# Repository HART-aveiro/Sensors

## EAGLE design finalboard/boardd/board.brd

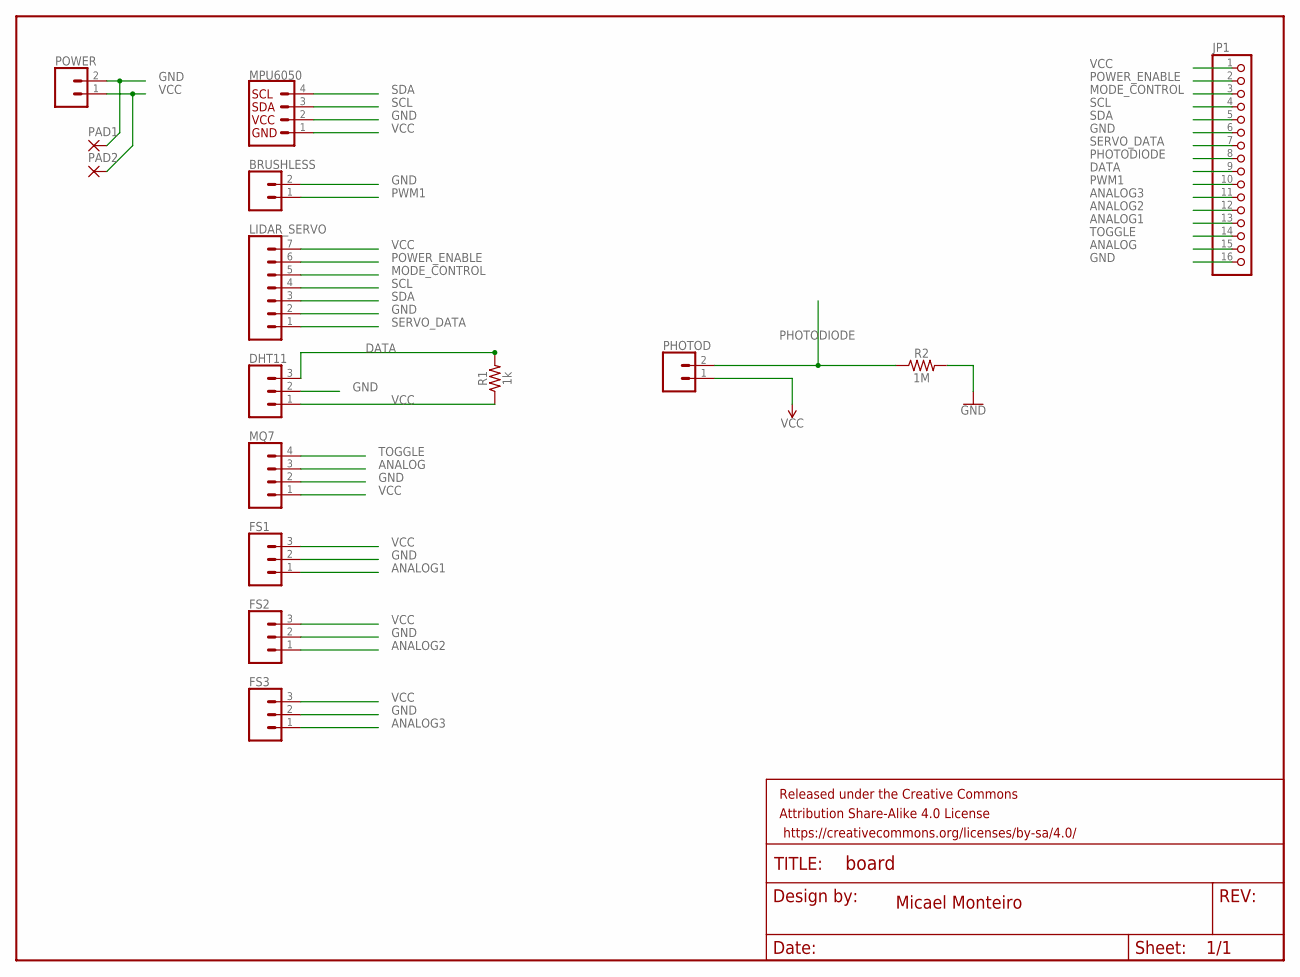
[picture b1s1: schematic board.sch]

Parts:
BRUSHLESS: CONN_02; 1X02
DHT11: CONN_03; 1X03
FRAME1: FRAME-LETTER; CREATIVE_COMMONS
FS1, FS2, FS3: CONN_03; 1X03
JP1: PINHD-1X16; 1X16
LIDAR_SERVO: CONN_07; 1X07
MPU6050: I2C_STANDARD; 1X04
MQ7: CONN_04; 1X04
PAD1, PAD2: 1,6/0,9
PHOTOD: CONN_02; 1X02
POWER: CONN_02; 1X02
R1: 1k; 0603
R2: 1M; 0603

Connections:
ANALOG: JP1.15, MQ7.3
ANALOG1: FS1.1, JP1.13
ANALOG2: FS2.1, JP1.12
ANALOG3: FS3.1, JP1.11
DATA: DHT11.3, JP1.9, R1.2
GND: BRUSHLESS.2, DHT11.2, FS1.2, FS2.2, FS3.2, JP1.6, JP1.16, LIDAR_SERVO.2, MPU6050.2, MQ7.2, PAD1.1, POWER.2, R2.2
MODE_CONTROL: JP1.3, LIDAR_SERVO.5
PHOTODIODE: JP1.8, PHOTOD.2, R2.1
POWER_ENABLE: JP1.2, LIDAR_SERVO.6
PWM1: BRUSHLESS.1, JP1.10
SCL: JP1.4, LIDAR_SERVO.4, MPU6050.3
SDA: JP1.5, LIDAR_SERVO.3, MPU6050.4
SERVO_DATA: JP1.7, LIDAR_SERVO.1
TOGGLE: JP1.14, MQ7.4
VCC: DHT11.1, FS1.3, FS2.3, FS3.3, JP1.1, LIDAR_SERVO.7, MPU6050.1, MQ7.1, PAD2.1, PHOTOD.1, POWER.1, R1.1

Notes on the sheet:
Micael Monteiro

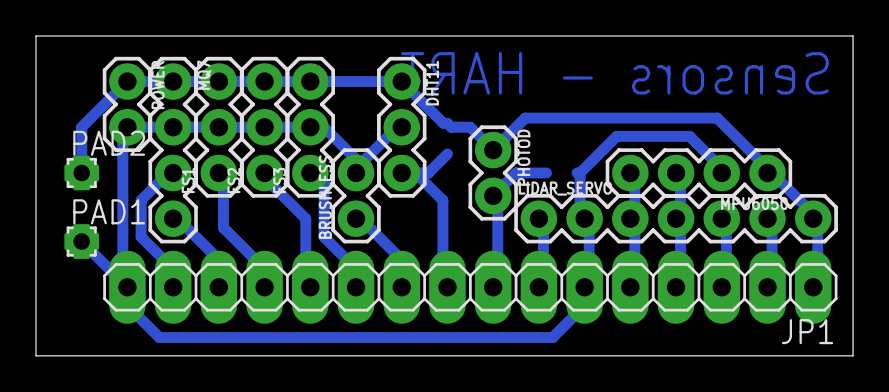
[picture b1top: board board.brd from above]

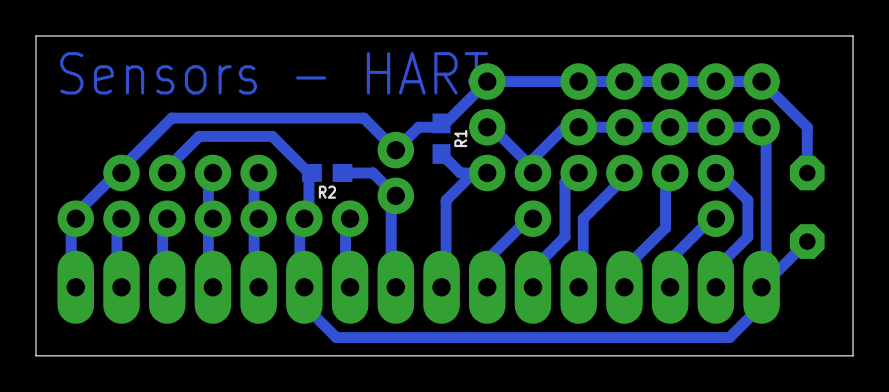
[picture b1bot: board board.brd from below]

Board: 2 copper layers, 45.4 x 17.8 mm, 16 parts (2 on the bottom side), 15 nets.

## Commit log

2017-04-26 Change main file name
2017-04-26 Added temp/hum lib
2017-04-28 Added dht11 code
2017-04-28 Added servo and brushless
2017-05-02 Total reshape of the code//Servo and brushless problem solved, Added simple feedback to brushless speed
2017-05-02 Working brush, servo, dht, mpu with debug from LEDs
2017-05-03 brushless velocity
2017-05-03 speedtrig functions added to hartimu
2017-05-03 Added MQ7 and corrected folders created by mistake
2017-05-03 PCB and flame sensors
2017-05-03 Added pcb files plus fire sensor API
2017-05-03 Added micael's work on flame sensor
2017-05-03 Temperature and humidity API
2017-05-03 Something happened and brushless atopped working :'(
2017-05-03 Semi works, problems in timing again :'(
2017-05-04 comunication code lines
2017-05-04 Working LIDAR @ 250HZ
2017-05-05 Latex documentation
2017-05-05 Removal of documentation
2017-05-05 Latex files
2017-05-05 removal
2017-05-05 removal latex files
2017-05-06 Corrected an error on line 420, bufMPU instead of bufLIDAR
2017-05-16 Not working
2017-05-17 Major changes to the code
2017-05-20 Comm working without lidar, new interrupt work method
2017-05-20 created gitIgnore for eagle's file
2017-05-20 All sensors working with comm without LIDAR
2017-05-20 Something is putting interrupt down
2017-05-20 conversa pedro
2017-05-20 Nao funciona e nao percebo porque, no comm, just MPU still fails, maybe an hardware problem, but don't know what it is :'(
2017-05-21 Deleted a empty line and added my email to git config
2017-05-23 Added lidar arduino code, need to test interrupt and ajust the time to 2778us Next step, introduce control from another arduino
2017-05-23 sensors.ino before correct freq
2017-05-23 Works all sensors without lidar, comm and pwm servos too
2017-05-23 Problems in MPU6050
2017-05-23 before pull
2017-05-24 Timer working at 360Hz
2017-05-24 Control for mega and lidar for uno without tests
2017-05-24 contact problems while testing
2017-05-26 working with voltage divider on pwm to servo
2017-05-26 working both arduino comm and sweep servo
2017-05-29 Sweep not working
2017-05-29 hartimu corrected
2017-05-29 Before upload after panda
2017-05-29 Sweep corrected but problems in timings
2017-05-29 Working LIDAR, sweep and brushless without comm
2017-05-31 all commented except lidar on loop
2017-05-31 Control is working, need a tweak
2017-05-31 Working with comm problems
2017-06-01 problems in com between arduinos
2017-06-02 BEfore pull after panda and patricia
2017-06-02 Change code in sensors and control just for a simple comm setup but still isn't working
2017-06-03 Code redone
2017-06-03 working moreless
2017-06-03 problems in sweep on top part, need some tweaks to unstuck, don't know what to do but lidar makes full reading from bottom to top
2017-06-03 smoothing percentage alteration
2017-06-03 cleaned the code a bit
2017-06-05 Tested and working, problem on top angles, but retrieves a good image
2017-06-11 final example code
2017-06-19 exemplo do brushless
2017-06-19 added pwmservo.h
2017-06-20 clean up
2017-06-20 upload final sensors board

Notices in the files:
parts and their libraries:
SparkFun-Connectors: Licensing: Creative Commons ShareAlike 4.0 International - https://creativecommons.org/licenses/by-sa/4.0
SparkFun-Aesthetics: Released under the Creative Commons Attribution Share-Alike 4.0 License
SparkFun-Aesthetics: https://creativecommons.org/licenses/by-sa/4.0
